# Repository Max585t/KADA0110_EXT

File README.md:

# KADA0110_EXT
Kada0110_ext is an extended 65% mechanical keyboard. It started as a remix of [Kada 0110](https://www.printables.com/model/891673-kada-0110-a-retro-inspired-65-mechanical-keyboard) by [Emil](https://www.printables.com/@Emil_28197). It has support for stepped left control and split backspace. PCB was designed by me. Case modifications also done by me. 

## BOM

| components | quaninty | link |
|----|----|----|
| PCB | 1 | https://github.com/Max585t/KADA0110_EXT/tree/main/Kicad |
| Case | 1 | https://github.com/Max585t/KADA0110_EXT/tree/main/3D%20Model/kada-0110-ext%20parts |
| 80x4x3mm Poron foam gaskets | 12 | [kprepublic.com/products/kprepublic-gasket-strip-gasket-pad-pads-stickers-foam-poron-material-for-mechanical-keyboard-le20-black-thick-round-corner?variant=43459474227363](https://kprepublic.com/products/kprepublic-gasket-strip-gasket-pad-pads-stickers-foam-poron-material-for-mechanical-keyboard-le20-black-thick-round-corner?variant=43459474227363) |

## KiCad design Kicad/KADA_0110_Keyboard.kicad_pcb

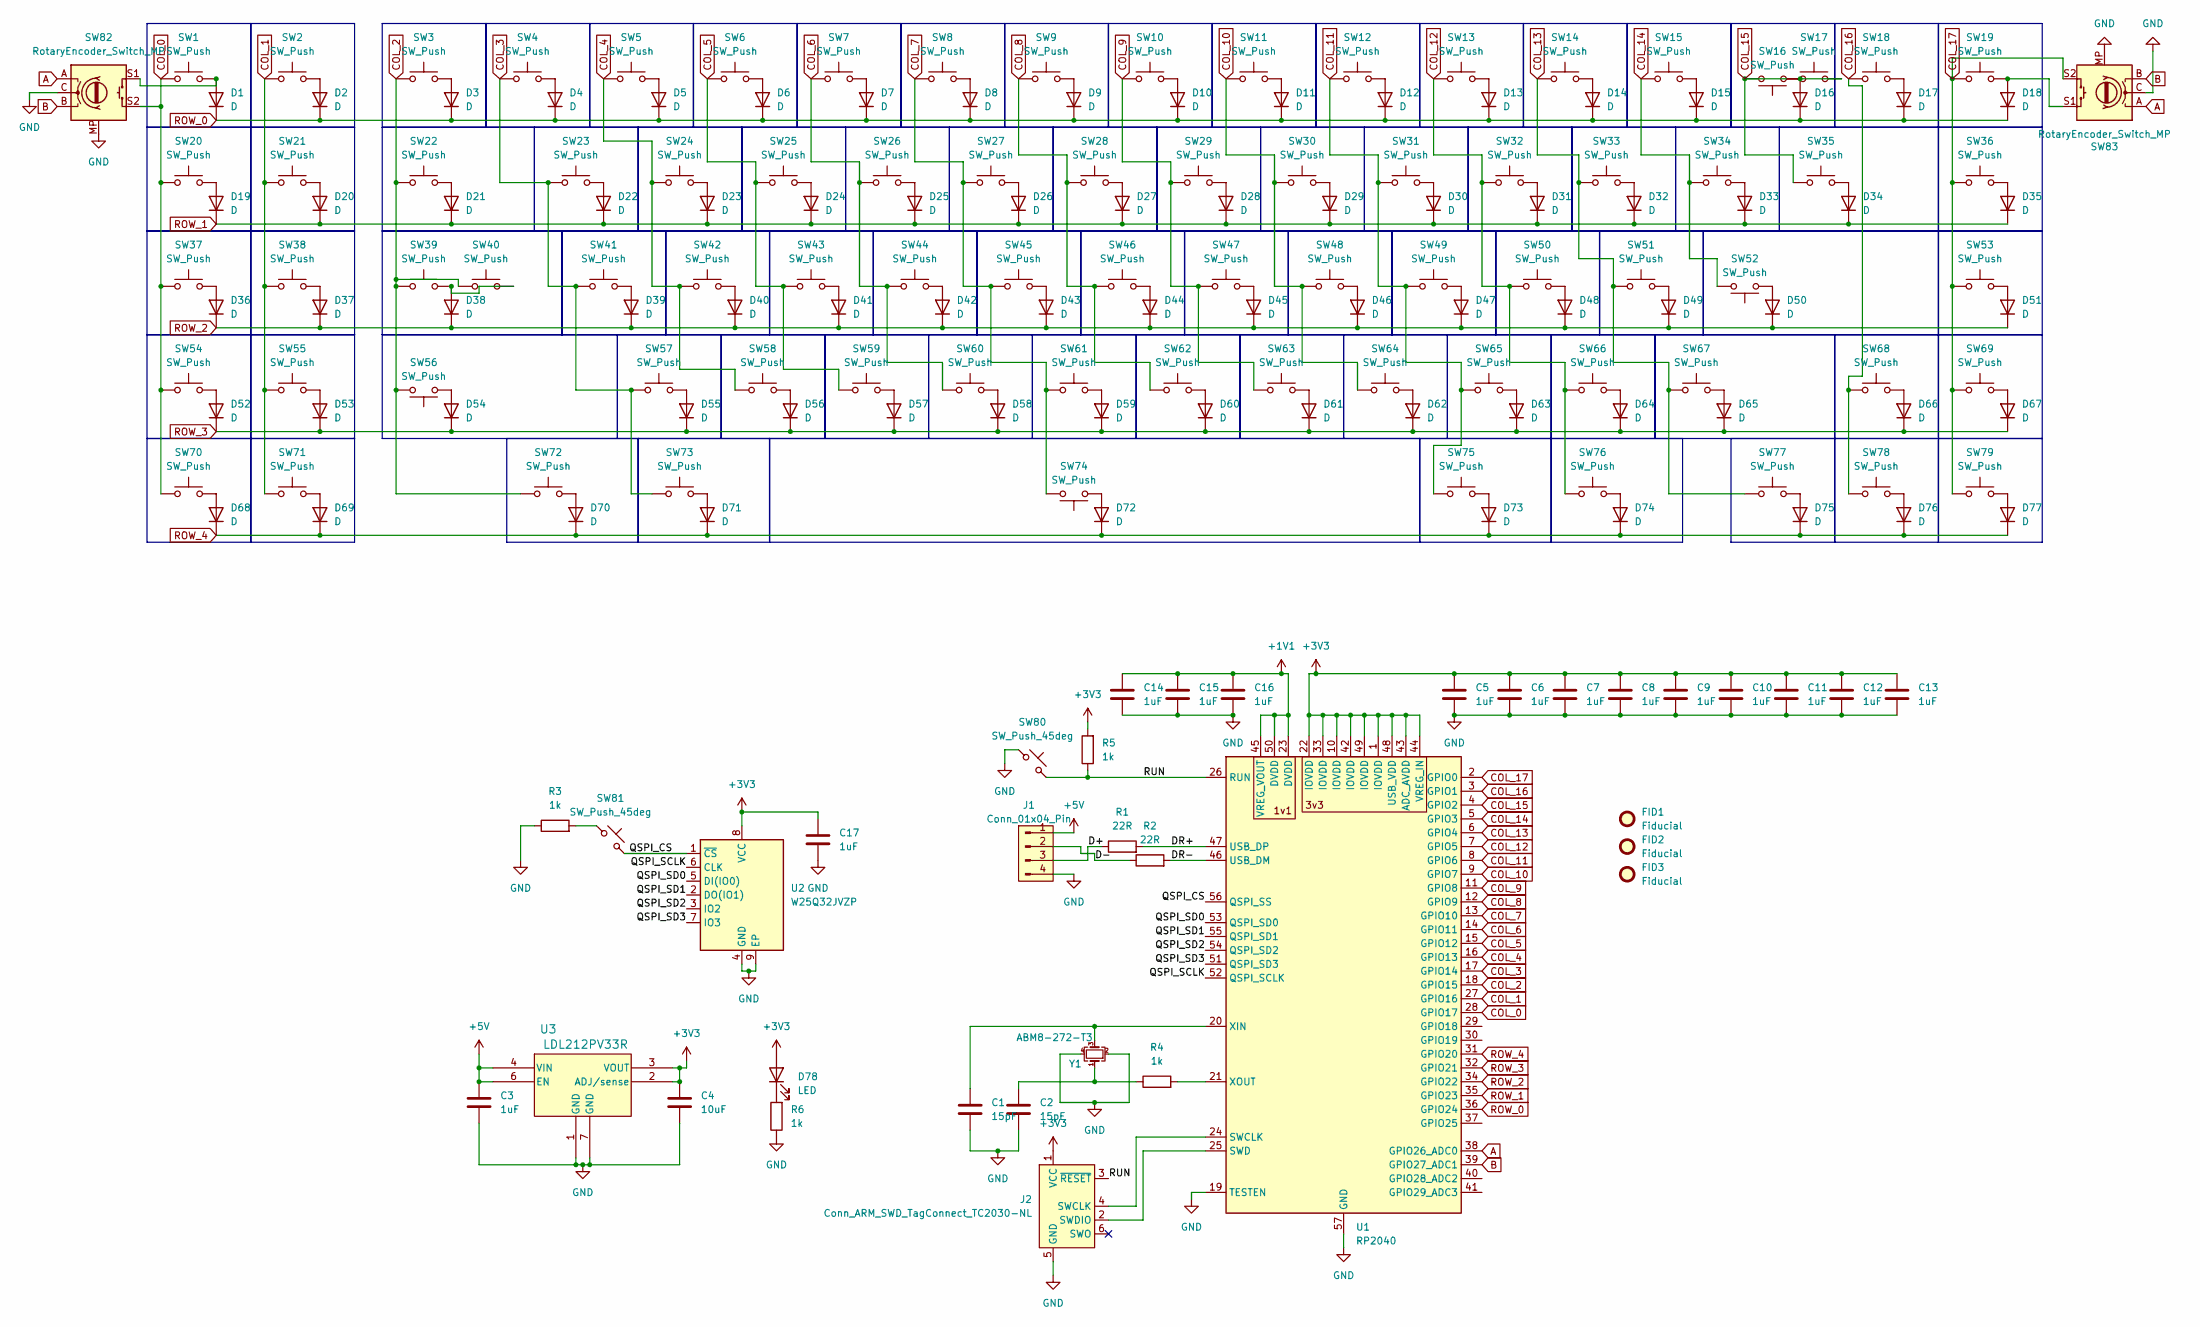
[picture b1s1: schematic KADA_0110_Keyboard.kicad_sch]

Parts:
C1, C2: 15pF; C_0402_1005Metric
C3, C5, C6, C7, C8, C9, C10, C11, C12, C13, C14, C15, C16, C17: 1uF; C_0402_1005Metric
C4: 10uF; C_0603_1608Metric
D1, D2, D3, D4, D5, D6, D7, D8, D9, D10, D11, D12, D13, D14, D15, D16, D17, D18, D19, D20, D21, D22, D23, D24, D25, D26, D27, D28, D29, D30, D31, D32, D33, D34, D35, D36, D37, D38, D39, D40, D41, D42, D43, D44, D45, D46, D47, D48, D49, D50, D51, D52, D53, D54, D55, D56, D57, D58, D59, D60, D61, D62, D63, D64, D65, D66, D67, D68, D69, D70, D71, D72, D73, D74, D75, D76, D77: D; D_SOD-123
D78: LED; LED_0603_1608Metric
FID1, FID2, FID3: Fiducial; Fiducial_1mm_Mask2mm
J1: Conn_01x04_Pin; JST_SH_SM04B-SRSS-TB_1x04-1MP_P1.00mm_Horizontal
J2: Conn_ARM_SWD_TagConnect_TC2030-NL; Tag-Connect_TC2030-IDC-NL_2x03_P1.27mm_Vertical
R1, R2: 22R; R_0402_1005Metric
R3, R4, R5, R6: 1k; L_0402_1005Metric
SW1, SW2, SW3, SW4, SW5, SW6, SW7, SW8, SW9, SW10, SW11, SW12, SW13, SW14, SW15, SW17, SW18, SW19, SW20, SW21, SW22, SW23, SW24, SW25, SW26, SW27, SW28, SW29, SW30, SW31, SW32, SW33, SW34, SW35, SW36, SW37, SW38, SW39, SW40, SW41, SW42, SW43, SW44, SW45, SW46, SW47, SW48, SW49, SW50, SW51, SW53, SW54, SW55, SW57, SW58, SW59, SW60, SW61, SW62, SW63, SW64, SW65, SW66, SW67, SW68, SW69, SW70, SW71, SW72, SW73, SW75, SW76, SW77, SW78, SW79: SW_Push; MX-Solderable-1U
SW16: SW_Push; SW_Cherry_MX_2.00u_PCB
SW52, SW56: SW_Push; SW_Cherry_MX_2.25u_PCB
SW74: SW_Push; SW_Cherry_MX_6.25u_PCB
SW80, SW81: SW_Push_45deg; SW_Push_1P1T_NO_CK_KMR2
SW82: RotaryEncoder_Switch_MP; RotaryEncoder_Alps_EC11E-Switch_Vertical_H20mm
SW83: RotaryEncoder_Switch_MP; RotaryEncoder_Alps_EC11E-Switch_Vertical_H20m
U1: RP2040; QFN-56-1EP_7x7mm_P0.4mm_EP3.2x3.2mm
U2: W25Q32JVZP; WSON-8-1EP_6x5mm_P1.27mm_EP3.4x4.3mm
U3: LDL212PV33R; DFN_V33R_STM
Y1: ABM8-272-T3; Crystal_SMD_3225-4Pin_3.2x2.5mm

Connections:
+1V1: C14.1, C15.1, C16.1, U1.23 (DVDD), U1.45 (VREG_VOUT), U1.50 (DVDD)
+3V3: C4.1, C5.1, C6.1, C7.1, C8.1, C9.1, C10.1, C11.1, C12.1, C13.1, C17.1, D78.2 (A), J2.1 (VCC), R5.2, U1.1 (IOVDD), U1.10 (IOVDD), U1.22 (IOVDD), U1.33 (IOVDD), U1.42 (IOVDD), U1.43 (ADC_AVDD), U1.44 (VREG_IN), U1.48 (USB_VDD), U1.49 (IOVDD), U2.8 (VCC), U3.2 (ADJ/sense), U3.3 (VOUT)
+5V: C3.1, J1.1, U3.4 (VIN), U3.6 (EN)
/D+: J1.3, R1.1
/D-: J1.2, R2.1
/DR+: R1.2, U1.47 (USB_DP)
/DR-: R2.2, U1.46 (USB_DM)
/QSPI_CS: SW81.2, U1.56 (QSPI_SS), U2.1 (~CS)
/QSPI_SCLK: U1.52 (QSPI_SCLK), U2.6 (CLK)
/QSPI_SD0: U1.53 (QSPI_SD0), U2.5 (DI(IO0))
/QSPI_SD1: U1.55 (QSPI_SD1), U2.2 (DO(IO1))
/QSPI_SD2: U1.54 (QSPI_SD2), U2.3 (IO2)
/QSPI_SD3: U1.51 (QSPI_SD3), U2.7 (IO3)
/RUN: J2.3 (~RESET), R5.1, SW80.2, U1.26 (RUN)
A: SW82.A, SW83.A, U1.38 (GPIO26_ADC0)
B: SW82.B, SW83.B, U1.39 (GPIO27_ADC1)
COL_0: SW1.1, SW20.1, SW37.1, SW54.1, SW70.1, SW82.S2, U1.28 (GPIO17)
COL_1: SW2.1, SW21.1, SW38.1, SW55.1, SW71.1, U1.27 (GPIO16)
COL_2: SW3.1, SW22.1, SW39.1, SW40.1, SW56.2, SW72.1, U1.18 (GPIO15)
COL_3: SW4.1, SW23.1, SW41.1, SW57.1, SW73.1, U1.17 (GPIO14)
COL_4: SW5.1, SW24.1, SW42.1, SW58.1, U1.16 (GPIO13)
COL_5: SW6.1, SW25.1, SW43.1, SW59.1, U1.15 (GPIO12)
COL_6: SW7.1, SW26.1, SW44.1, SW60.1, U1.14 (GPIO11)
COL_7: SW8.1, SW27.1, SW45.1, SW61.1, SW74.2, U1.13 (GPIO10)
COL_8: SW9.1, SW28.1, SW46.1, SW62.1, U1.12 (GPIO9)
COL_9: SW10.1, SW29.1, SW47.1, SW63.1, U1.11 (GPIO8)
COL_10: SW11.1, SW30.1, SW48.1, SW64.1, U1.9 (GPIO7)
COL_11: SW12.1, SW31.1, SW49.1, SW65.1, SW75.1, U1.8 (GPIO6)
COL_12: SW13.1, SW32.1, SW50.1, SW66.1, SW76.1, U1.7 (GPIO5)
COL_13: SW14.1, SW33.1, SW51.1, SW67.1, SW77.1, U1.6 (GPIO4)
COL_14: SW15.1, SW34.1, SW52.2, U1.5 (GPIO3)
COL_15: SW16.2, SW17.1, SW35.1, U1.4 (GPIO2)
COL_16: SW18.1, SW68.1, SW78.1, U1.3 (GPIO1)
COL_17: SW19.1, SW36.1, SW53.1, SW69.1, SW79.1, SW83.S2, U1.2 (GPIO0)
GND: C1.2, C2.2, C3.2, C4.2, C5.2, C6.2, C7.2, C8.2, C9.2, C10.2, C11.2, C12.2, C13.2, C14.2, C15.2, C16.2, C17.2, J1.4, J2.5 (GND), R3.1, R6.1, SW80.1, SW82.C, SW82.MP, SW83.C, SW83.MP, U1.19 (TESTEN), U1.57 (GND), U2.4 (GND), U2.9 (EP), U3.1 (GND), U3.7 (GND), Y1.2, Y1.4
unnamed: C2.1, R4.1, Y1.1
unnamed: D1.2 (A), SW1.2, SW82.S1
unnamed: D2.2 (A), SW2.2
unnamed: D3.2 (A), SW3.2
unnamed: D4.2 (A), SW4.2
unnamed: D5.2 (A), SW5.2
unnamed: D6.2 (A), SW6.2
unnamed: D7.2 (A), SW7.2
unnamed: D8.2 (A), SW8.2
unnamed: D9.2 (A), SW9.2
unnamed: D10.2 (A), SW10.2
unnamed: D11.2 (A), SW11.2
unnamed: D12.2 (A), SW12.2
unnamed: D13.2 (A), SW13.2
unnamed: D14.2 (A), SW14.2
unnamed: D15.2 (A), SW15.2
unnamed: D16.2 (A), SW16.1, SW17.2
unnamed: D17.2 (A), SW18.2
unnamed: D18.2 (A), SW19.2, SW83.S1
unnamed: D19.2 (A), SW20.2
unnamed: D20.2 (A), SW21.2
unnamed: D21.2 (A), SW22.2
unnamed: D22.2 (A), SW23.2
unnamed: D23.2 (A), SW24.2
unnamed: D24.2 (A), SW25.2
unnamed: D25.2 (A), SW26.2
unnamed: D26.2 (A), SW27.2
unnamed: D27.2 (A), SW28.2
unnamed: D28.2 (A), SW29.2
unnamed: D29.2 (A), SW30.2
unnamed: D30.2 (A), SW31.2
unnamed: D31.2 (A), SW32.2
unnamed: D32.2 (A), SW33.2
unnamed: D33.2 (A), SW34.2
unnamed: D34.2 (A), SW35.2
unnamed: D35.2 (A), SW36.2
unnamed: D36.2 (A), SW37.2
unnamed: D37.2 (A), SW38.2
unnamed: D38.2 (A), SW39.2, SW40.2
unnamed: D39.2 (A), SW41.2
unnamed: D40.2 (A), SW42.2
unnamed: D41.2 (A), SW43.2
unnamed: D42.2 (A), SW44.2
unnamed: D43.2 (A), SW45.2
unnamed: D44.2 (A), SW46.2
unnamed: D45.2 (A), SW47.2
unnamed: D46.2 (A), SW48.2
unnamed: D47.2 (A), SW49.2
unnamed: D48.2 (A), SW50.2
unnamed: D49.2 (A), SW51.2
unnamed: D50.2 (A), SW52.1
unnamed: D51.2 (A), SW53.2
unnamed: D52.2 (A), SW54.2
unnamed: D53.2 (A), SW55.2
unnamed: D54.2 (A), SW56.1
unnamed: D55.2 (A), SW57.2
unnamed: D56.2 (A), SW58.2
unnamed: D57.2 (A), SW59.2
unnamed: D58.2 (A), SW60.2
unnamed: D59.2 (A), SW61.2
unnamed: D60.2 (A), SW62.2
unnamed: D61.2 (A), SW63.2
unnamed: D62.2 (A), SW64.2
unnamed: D63.2 (A), SW65.2
unnamed: D64.2 (A), SW66.2
unnamed: D65.2 (A), SW67.2
unnamed: D66.2 (A), SW68.2
unnamed: D67.2 (A), SW69.2
unnamed: D68.2 (A), SW70.2
unnamed: D69.2 (A), SW71.2
unnamed: D70.2 (A), SW72.2
unnamed: D71.2 (A), SW73.2
unnamed: D72.2 (A), SW74.1
unnamed: D73.2 (A), SW75.2
unnamed: D74.2 (A), SW76.2
unnamed: D75.2 (A), SW77.2
unnamed: D76.2 (A), SW78.2
unnamed: D77.2 (A), SW79.2
unnamed: D78.1 (K), R6.2
unnamed: J2.4 (SWCLK), U1.24 (SWCLK)
unnamed: J2.2 (SWDIO), U1.25 (SWD)
unnamed: R3.2, SW81.1
unnamed: C1.1, U1.20 (XIN), Y1.3
unnamed: R4.2, U1.21 (XOUT)
ROW_0: D1.1 (K), D2.1 (K), D3.1 (K), D4.1 (K), D5.1 (K), D6.1 (K), D7.1 (K), D8.1 (K), D9.1 (K), D10.1 (K), D11.1 (K), D12.1 (K), D13.1 (K), D14.1 (K), D15.1 (K), D16.1 (K), D17.1 (K), D18.1 (K), U1.36 (GPIO24)
ROW_1: D19.1 (K), D20.1 (K), D21.1 (K), D22.1 (K), D23.1 (K), D24.1 (K), D25.1 (K), D26.1 (K), D27.1 (K), D28.1 (K), D29.1 (K), D30.1 (K), D31.1 (K), D32.1 (K), D33.1 (K), D34.1 (K), D35.1 (K), U1.35 (GPIO23)
ROW_2: D36.1 (K), D37.1 (K), D38.1 (K), D39.1 (K), D40.1 (K), D41.1 (K), D42.1 (K), D43.1 (K), D44.1 (K), D45.1 (K), D46.1 (K), D47.1 (K), D48.1 (K), D49.1 (K), D50.1 (K), D51.1 (K), U1.34 (GPIO22)
ROW_3: D52.1 (K), D53.1 (K), D54.1 (K), D55.1 (K), D56.1 (K), D57.1 (K), D58.1 (K), D59.1 (K), D60.1 (K), D61.1 (K), D62.1 (K), D63.1 (K), D64.1 (K), D65.1 (K), D66.1 (K), D67.1 (K), U1.32 (GPIO21)
ROW_4: D68.1 (K), D69.1 (K), D70.1 (K), D71.1 (K), D72.1 (K), D73.1 (K), D74.1 (K), D75.1 (K), D76.1 (K), D77.1 (K), U1.31 (GPIO20)

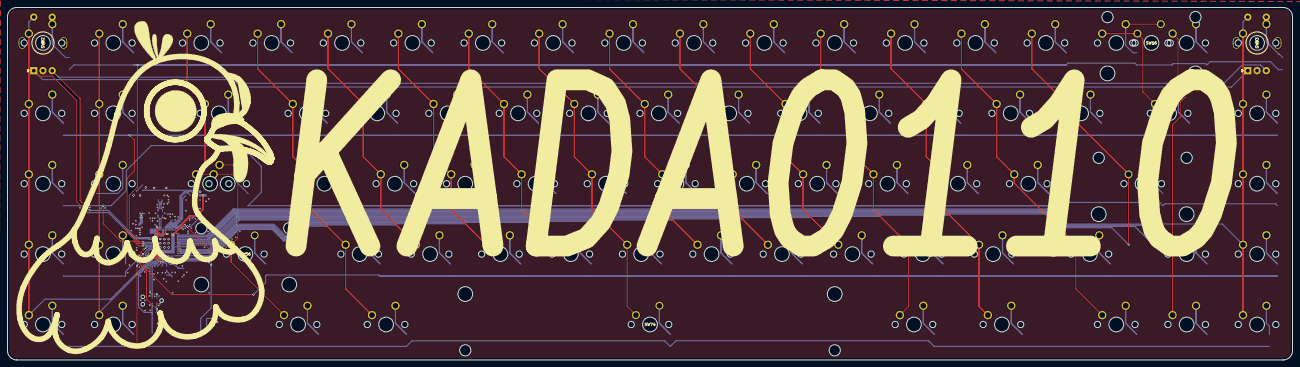
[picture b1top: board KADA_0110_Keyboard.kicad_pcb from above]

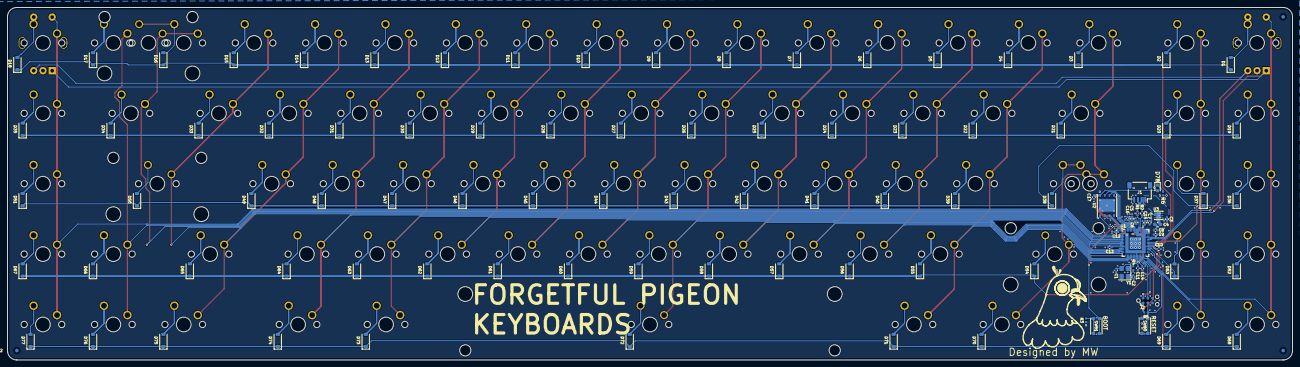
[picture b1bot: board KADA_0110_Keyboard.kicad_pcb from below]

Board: 2 copper layers, 347.8 x 95.4 mm, 193 parts (112 on the bottom side), 124 nets.

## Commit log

2025-11-10 Add 3v3 LED and fix font
2025-11-10 Add 3d models
2025-11-10 Move pcb
